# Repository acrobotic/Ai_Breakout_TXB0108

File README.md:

## Ai\_Breakout\_TXB0108

PCB design files (EAGLE) for a breakout board of the 8-channel bi-directional
Logic Level Shifter TXB0108.

## Description

For more details, check out the product page at:

   * https://acrobotic.com/brk-00014

Designed by ACROBOTIC Industries.  Please consider buying products from us to 
help fund future Open-Source projects like this! We’ll always put our best 
effort in every project, and release all our design files and code for you to 
use. 

## License

Released under the Creative Commons Attribution, Share-Alike license. Please 
check LICENSE.txt for more information. All text above must be included in any 
redistribution.

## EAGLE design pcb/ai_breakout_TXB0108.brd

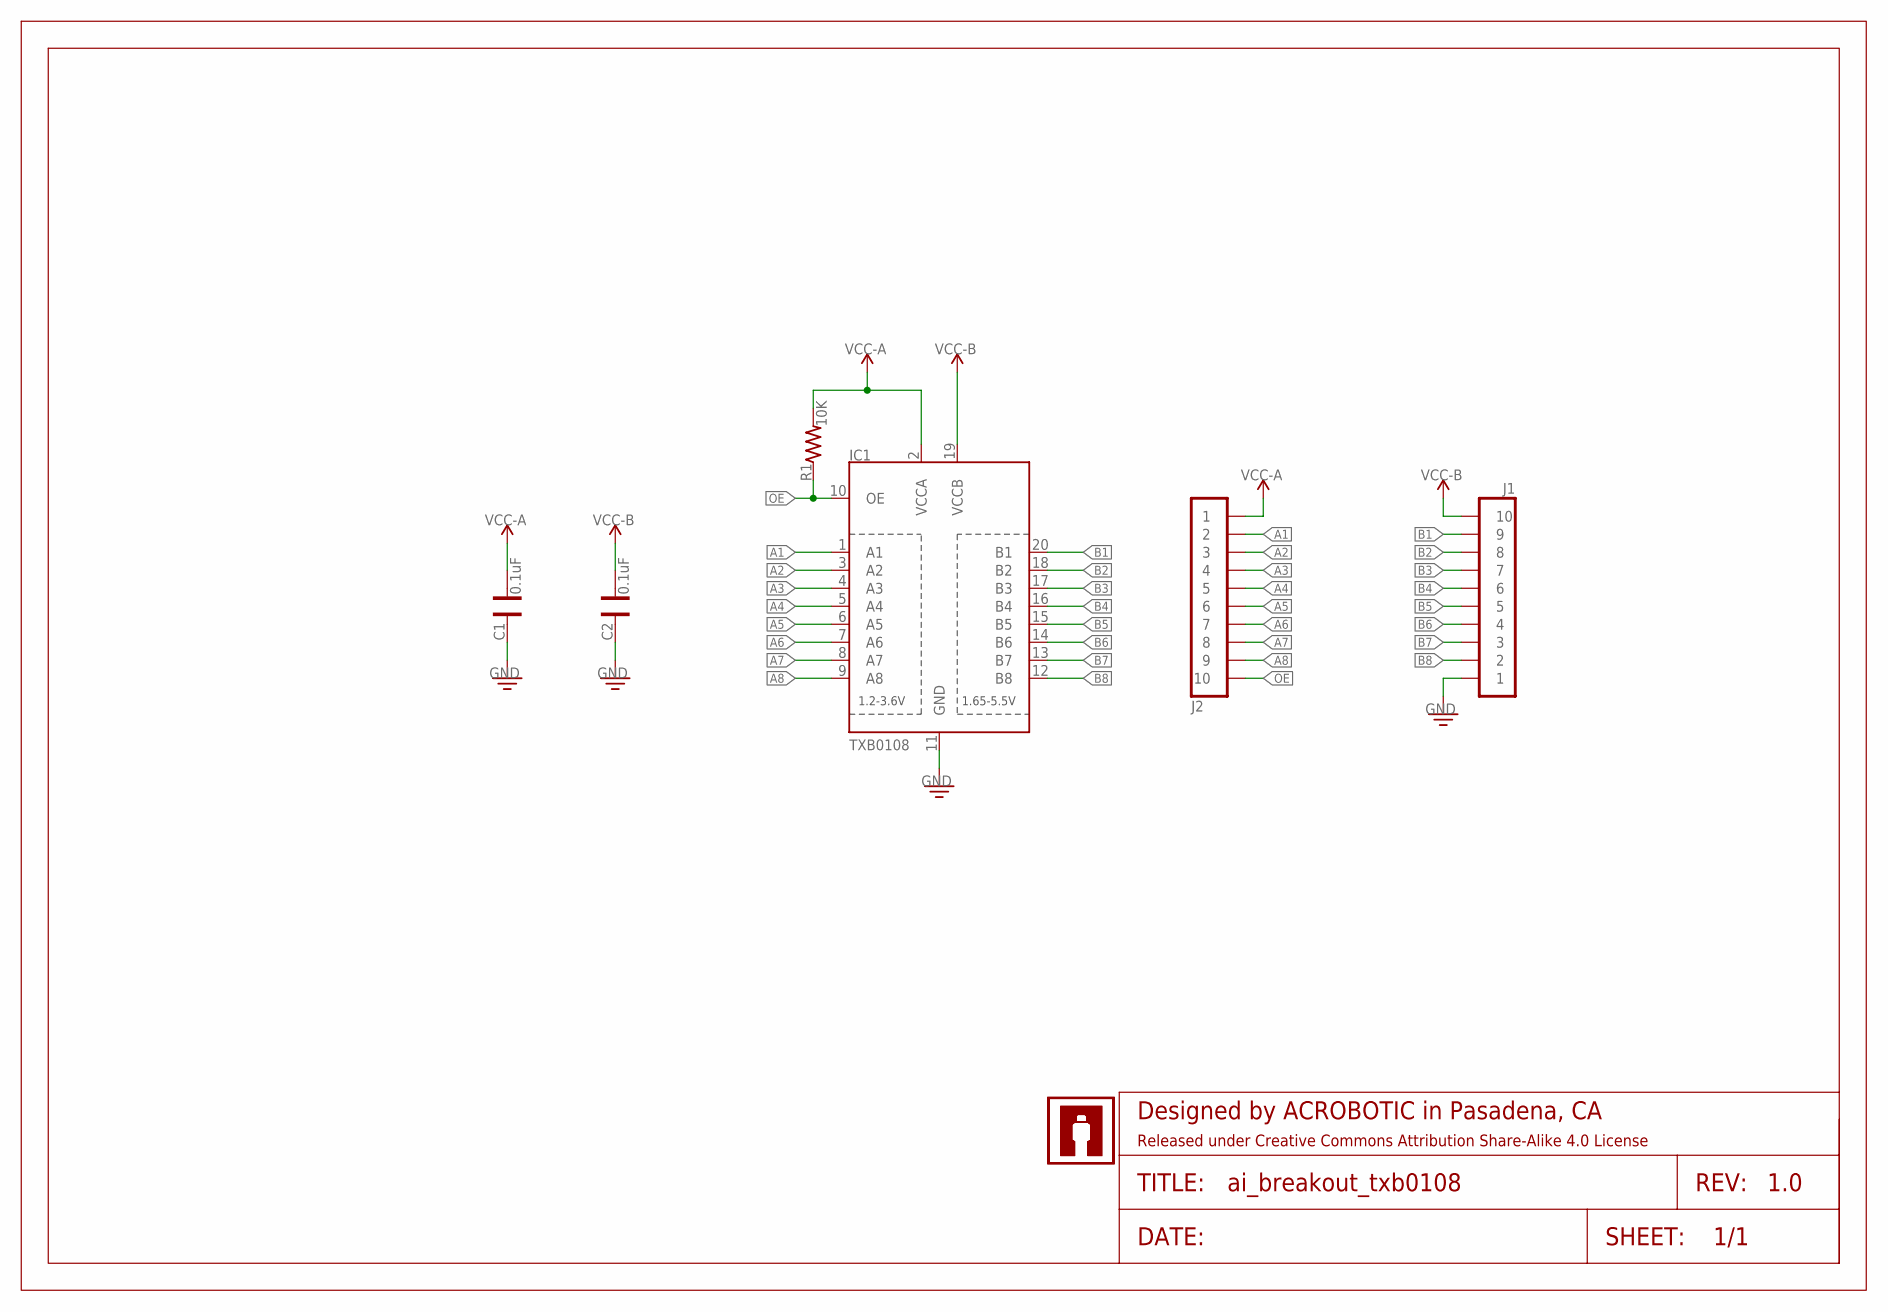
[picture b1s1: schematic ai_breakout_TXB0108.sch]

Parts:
C1, C2: 0.1uF; CAP-0603
FRAME1: FRAME-LETTER; CREATIVE-COMMONS
IC1: TXB0108; TSSOP20
J1: 1X10
J2: 1X10NOFIRST; 1X10-NOFIRST
R1: 10K; RES-0603
U$1, U$2: AI-LOGOXS; AI-LOGO-XS

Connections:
A1: IC1.1 (A1), J2.2
A2: IC1.3 (A2), J2.3
A3: IC1.4 (A3), J2.4
A4: IC1.5 (A4), J2.5
A5: IC1.6 (A5), J2.6
A6: IC1.7 (A6), J2.7
A7: IC1.8 (A7), J2.8
A8: IC1.9 (A8), J2.9
B1: IC1.20 (B1), J1.9
B2: IC1.18 (B2), J1.8
B3: IC1.17 (B3), J1.7
B4: IC1.16 (B4), J1.6
B5: IC1.15 (B5), J1.5
B6: IC1.14 (B6), J1.4
B7: IC1.13 (B7), J1.3
B8: IC1.12 (B8), J1.2
GND: C1.2, C2.2, IC1.11 (GND), J1.1
OE: IC1.10 (OE), J2.10, R1.1
VCC-A: C1.1, IC1.2 (VCCA), J2.1, R1.2
VCC-B: C2.1, IC1.19 (VCCB), J1.10

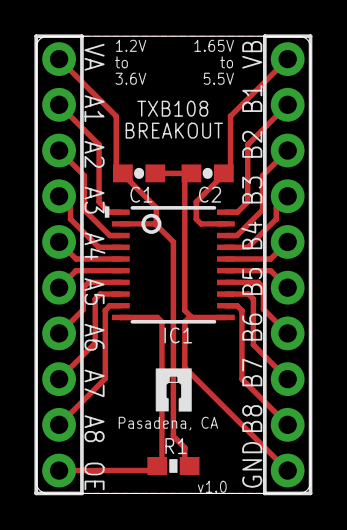
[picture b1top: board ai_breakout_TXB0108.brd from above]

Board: 2 copper layers, 15.2 x 25.4 mm, 9 parts (1 on the bottom side), 20 nets.

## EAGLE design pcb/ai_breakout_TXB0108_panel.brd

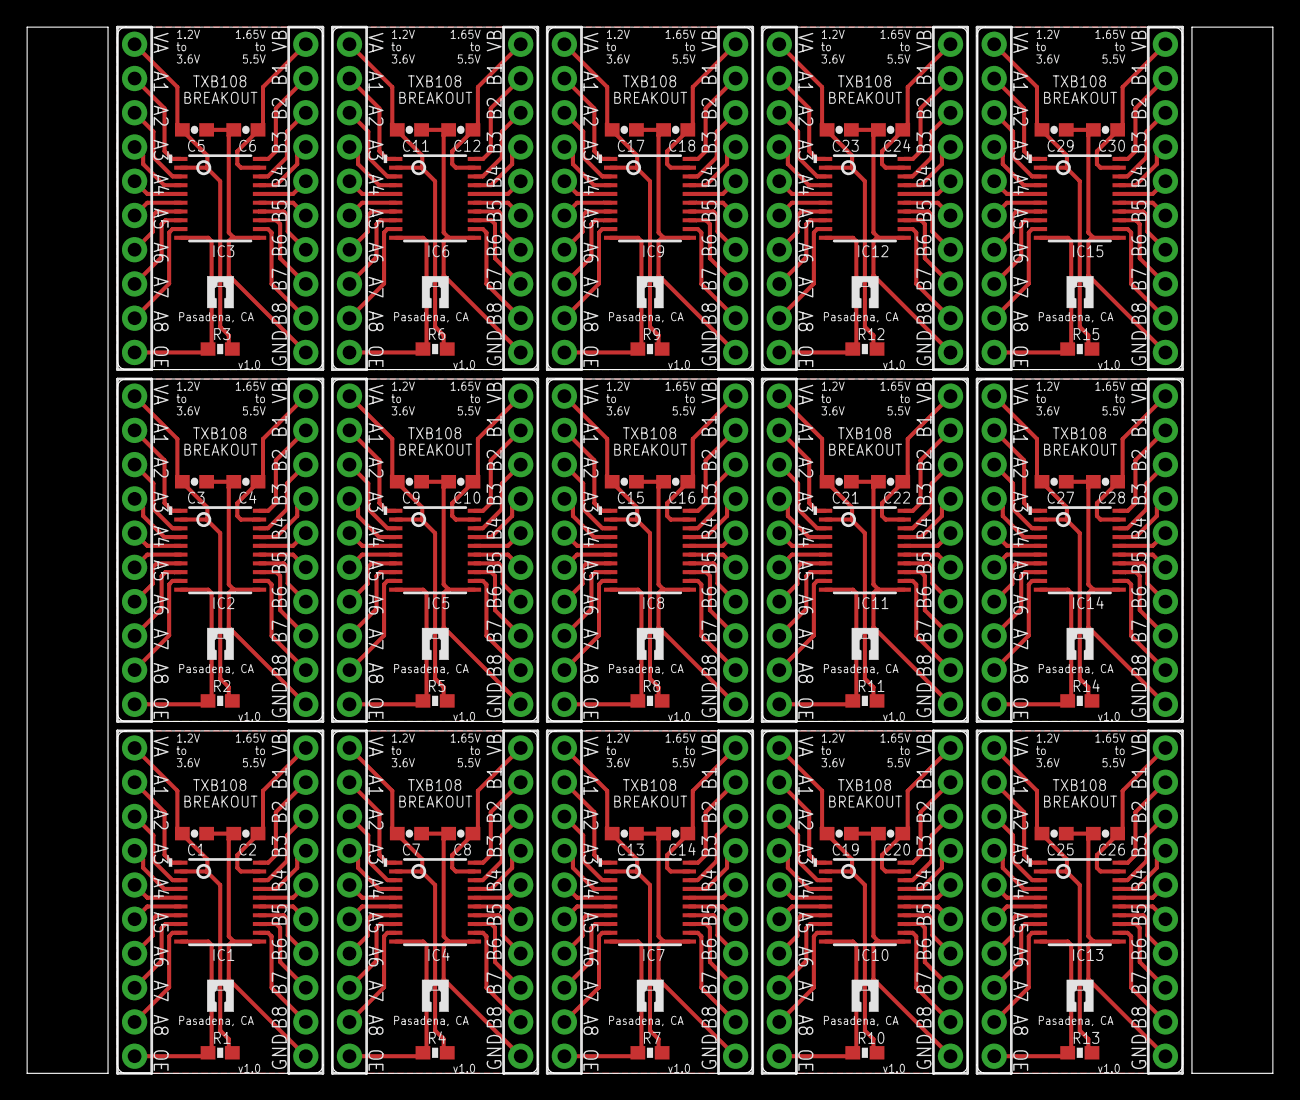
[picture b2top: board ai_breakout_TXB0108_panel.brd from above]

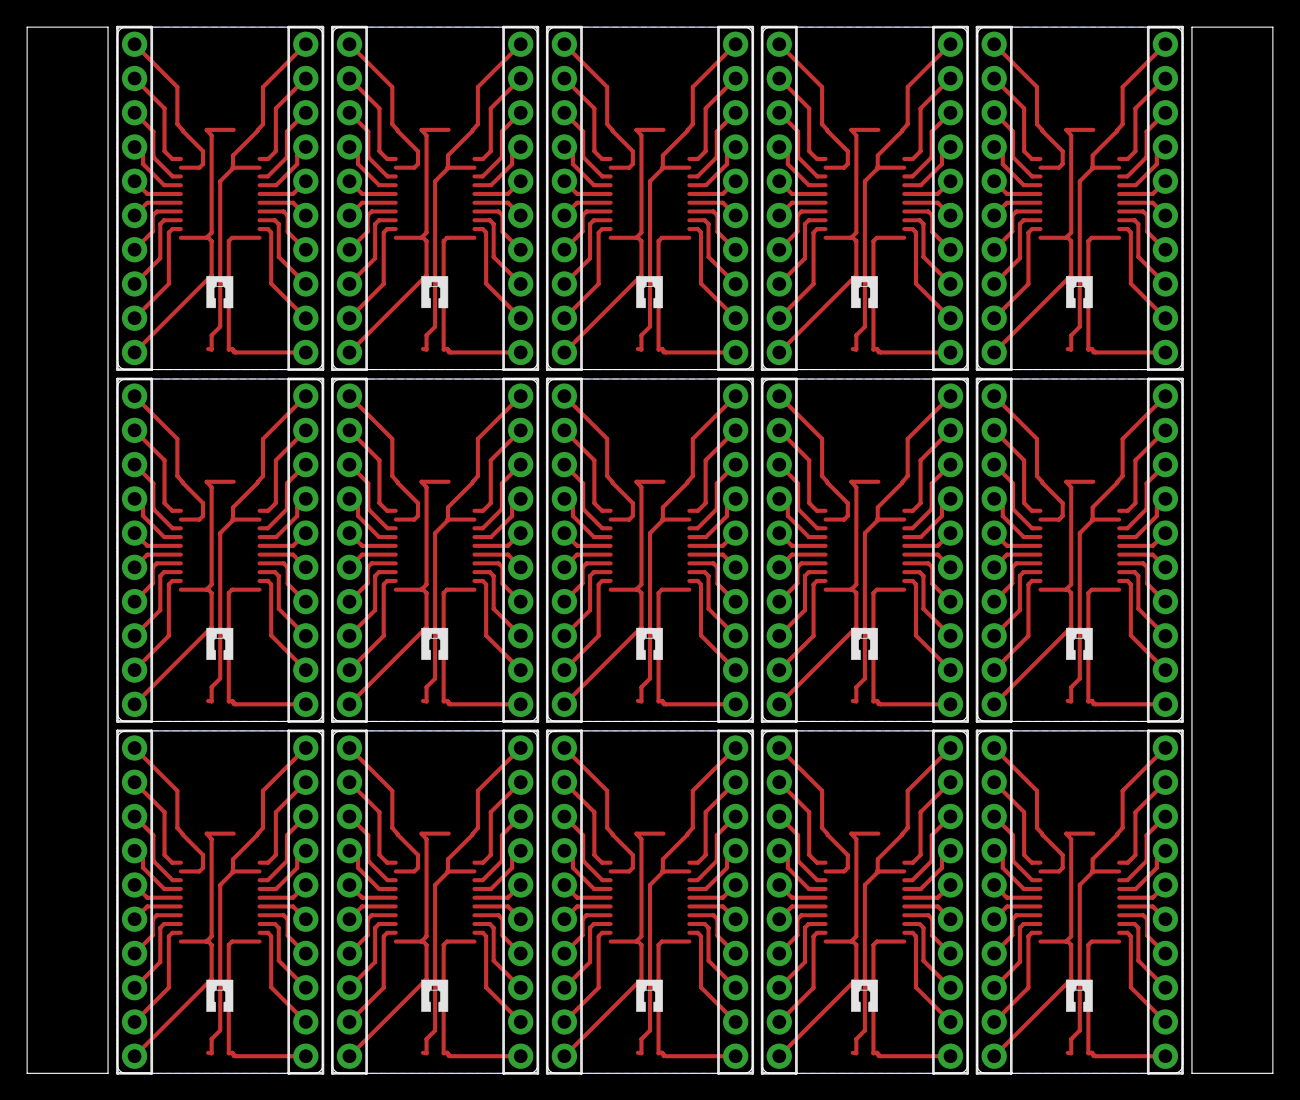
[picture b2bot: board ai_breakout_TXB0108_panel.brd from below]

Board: 2 copper layers, 92.4 x 77.6 mm, 121 parts (15 on the bottom side), 300 nets.

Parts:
C1, C2, C3, C4, C5, C6, C7, C8, C9, C10, C11, C12, C13, C14, C15, C16, C17, C18, C19, C20, C21, C22, C23, C24, C25, C26, C27, C28, C29, C30: 0.1uF; CAP-0603
FRAME1: FRAME-LETTER; CREATIVE-COMMONS
IC1, IC2, IC3, IC4, IC5, IC6, IC7, IC8, IC9, IC10, IC11, IC12, IC13, IC14, IC15: TXB0108; TSSOP20
J1, J3, J5, J7, J9, J11, J13, J15, J17, J19, J21, J23, J25, J27, J29: 1X10
J2, J4, J6, J8, J10, J12, J14, J16, J18, J20, J22, J24, J26, J28, J30: 1X10NOFIRST; 1X10-NOFIRST
R1, R2, R3, R4, R5, R6, R7, R8, R9, R10, R11, R12, R13, R14, R15: 10K; RES-0603
U$1, U$2, U$3, U$4, U$5, U$6, U$7, U$8, U$9, U$10, U$11, U$12, U$13, U$14, U$15, U$16, U$17, U$18, U$19, U$20, U$21, U$22, U$23, U$24, U$25, U$26, U$27, U$28, U$29, U$30: AI-LOGOXS; AI-LOGO-XS

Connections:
A1: IC1.1, J2.2
A2: IC1.3, J2.3
A3: IC1.4, J2.4
A4: IC1.5, J2.5
A5: IC1.6, J2.6
A6: IC1.7, J2.7
A7: IC1.8, J2.8
A8: IC1.9, J2.9
A9: IC2.1, J4.2
A10: IC2.3, J4.3
A11: IC2.4, J4.4
A12: IC2.5, J4.5
A13: IC2.6, J4.6
A14: IC2.7, J4.7
A15: IC2.8, J4.8
A16: IC2.9, J4.9
A17: IC3.1, J6.2
A18: IC3.3, J6.3
A19: IC3.4, J6.4
A20: IC3.5, J6.5
A21: IC3.6, J6.6
A22: IC3.7, J6.7
A23: IC3.8, J6.8
A24: IC3.9, J6.9
A25: IC4.1, J8.2
A26: IC4.3, J8.3
A27: IC4.4, J8.4
A28: IC4.5, J8.5
A29: IC4.6, J8.6
A30: IC4.7, J8.7
A31: IC4.8, J8.8
A32: IC4.9, J8.9
A33: IC5.1, J10.2
A34: IC5.3, J10.3
A35: IC5.4, J10.4
A36: IC5.5, J10.5
A37: IC5.6, J10.6
A38: IC5.7, J10.7
A39: IC5.8, J10.8
A40: IC5.9, J10.9
A41: IC6.1, J12.2
A42: IC6.3, J12.3
A43: IC6.4, J12.4
A44: IC6.5, J12.5
A45: IC6.6, J12.6
A46: IC6.7, J12.7
A47: IC6.8, J12.8
A48: IC6.9, J12.9
A49: IC7.1, J14.2
A50: IC7.3, J14.3
A51: IC7.4, J14.4
A52: IC7.5, J14.5
A53: IC7.6, J14.6
A54: IC7.7, J14.7
A55: IC7.8, J14.8
A56: IC7.9, J14.9
A57: IC8.1, J16.2
A58: IC8.3, J16.3
A59: IC8.4, J16.4
A60: IC8.5, J16.5
A61: IC8.6, J16.6
A62: IC8.7, J16.7
A63: IC8.8, J16.8
A64: IC8.9, J16.9
A65: IC9.1, J18.2
A66: IC9.3, J18.3
A67: IC9.4, J18.4
A68: IC9.5, J18.5
A69: IC9.6, J18.6
A70: IC9.7, J18.7
A71: IC9.8, J18.8
A72: IC9.9, J18.9
A73: IC10.1, J20.2
A74: IC10.3, J20.3
A75: IC10.4, J20.4
A76: IC10.5, J20.5
A77: IC10.6, J20.6
A78: IC10.7, J20.7
A79: IC10.8, J20.8
A80: IC10.9, J20.9
A81: IC11.1, J22.2
A82: IC11.3, J22.3
A83: IC11.4, J22.4
A84: IC11.5, J22.5
A85: IC11.6, J22.6
A86: IC11.7, J22.7
A87: IC11.8, J22.8
A88: IC11.9, J22.9
A89: IC12.1, J24.2
A90: IC12.3, J24.3
A91: IC12.4, J24.4
A92: IC12.5, J24.5
A93: IC12.6, J24.6
A94: IC12.7, J24.7
A95: IC12.8, J24.8
A96: IC12.9, J24.9
A97: IC13.1, J26.2
A98: IC13.3, J26.3
A99: IC13.4, J26.4
A100: IC13.5, J26.5
A101: IC13.6, J26.6
A102: IC13.7, J26.7
A103: IC13.8, J26.8
A104: IC13.9, J26.9
A105: IC14.1, J28.2
A106: IC14.3, J28.3
A107: IC14.4, J28.4
A108: IC14.5, J28.5
A109: IC14.6, J28.6
A110: IC14.7, J28.7
A111: IC14.8, J28.8
A112: IC14.9, J28.9
A113: IC15.1, J30.2
A114: IC15.3, J30.3
A115: IC15.4, J30.4
A116: IC15.5, J30.5
A117: IC15.6, J30.6
A118: IC15.7, J30.7
A119: IC15.8, J30.8
A120: IC15.9, J30.9
B1: IC1.20, J1.9
B2: IC1.18, J1.8
B3: IC1.17, J1.7
B4: IC1.16, J1.6
B5: IC1.15, J1.5
B6: IC1.14, J1.4
B7: IC1.13, J1.3
B8: IC1.12, J1.2
B9: IC2.12, J3.2
B10: IC2.13, J3.3
B11: IC2.14, J3.4
B12: IC2.15, J3.5
B13: IC2.16, J3.6
B14: IC2.17, J3.7
B15: IC2.18, J3.8
B16: IC2.20, J3.9
B17: IC3.12, J5.2
B18: IC3.13, J5.3
B19: IC3.14, J5.4
B20: IC3.15, J5.5
B21: IC3.16, J5.6
B22: IC3.17, J5.7
B23: IC3.18, J5.8
B24: IC3.20, J5.9
B25: IC4.12, J7.2
B26: IC4.13, J7.3
B27: IC4.14, J7.4
B28: IC4.15, J7.5
B29: IC4.16, J7.6
B30: IC4.17, J7.7
B31: IC4.18, J7.8
B32: IC4.20, J7.9
B33: IC5.12, J9.2
B34: IC5.13, J9.3
B35: IC5.14, J9.4
B36: IC5.15, J9.5
B37: IC5.16, J9.6
B38: IC5.17, J9.7
B39: IC5.18, J9.8
B40: IC5.20, J9.9
B41: IC6.12, J11.2
B42: IC6.13, J11.3
B43: IC6.14, J11.4
B44: IC6.15, J11.5
B45: IC6.16, J11.6
B46: IC6.17, J11.7
B47: IC6.18, J11.8
B48: IC6.20, J11.9
B49: IC7.12, J13.2
B50: IC7.13, J13.3
B51: IC7.14, J13.4
B52: IC7.15, J13.5
B53: IC7.16, J13.6
B54: IC7.17, J13.7
B55: IC7.18, J13.8
B56: IC7.20, J13.9
B57: IC8.12, J15.2
B58: IC8.13, J15.3
B59: IC8.14, J15.4
B60: IC8.15, J15.5
B61: IC8.16, J15.6
B62: IC8.17, J15.7
B63: IC8.18, J15.8
B64: IC8.20, J15.9
B65: IC9.12, J17.2
B66: IC9.13, J17.3
B67: IC9.14, J17.4
B68: IC9.15, J17.5
B69: IC9.16, J17.6
B70: IC9.17, J17.7
B71: IC9.18, J17.8
B72: IC9.20, J17.9
B73: IC10.12, J19.2
B74: IC10.13, J19.3
B75: IC10.14, J19.4
B76: IC10.15, J19.5
B77: IC10.16, J19.6
B78: IC10.17, J19.7
B79: IC10.18, J19.8
B80: IC10.20, J19.9
B81: IC11.12, J21.2
B82: IC11.13, J21.3
B83: IC11.14, J21.4
B84: IC11.15, J21.5
B85: IC11.16, J21.6
B86: IC11.17, J21.7
B87: IC11.18, J21.8
B88: IC11.20, J21.9
B89: IC12.12, J23.2
B90: IC12.13, J23.3
B91: IC12.14, J23.4
B92: IC12.15, J23.5
B93: IC12.16, J23.6
B94: IC12.17, J23.7
B95: IC12.18, J23.8
B96: IC12.20, J23.9
B97: IC13.12, J25.2
B98: IC13.13, J25.3
B99: IC13.14, J25.4
B100: IC13.15, J25.5
B101: IC13.16, J25.6
B102: IC13.17, J25.7
B103: IC13.18, J25.8
B104: IC13.20, J25.9
B105: IC14.12, J27.2
B106: IC14.13, J27.3
B107: IC14.14, J27.4
B108: IC14.15, J27.5
B109: IC14.16, J27.6
B110: IC14.17, J27.7
B111: IC14.18, J27.8
B112: IC14.20, J27.9
B113: IC15.12, J29.2
B114: IC15.13, J29.3
B115: IC15.14, J29.4
B116: IC15.15, J29.5
B117: IC15.16, J29.6
B118: IC15.17, J29.7
B119: IC15.18, J29.8
B120: IC15.20, J29.9
GND: C1.2, C2.2, IC1.11, J1.1
GND1: C3.2, C4.2, IC2.11, J3.1
GND2: C5.2, C6.2, IC3.11, J5.1
GND3: C7.2, C8.2, IC4.11, J7.1
GND4: C9.2, C10.2, IC5.11, J9.1
GND5: C11.2, C12.2, IC6.11, J11.1
GND6: C13.2, C14.2, IC7.11, J13.1
GND7: C15.2, C16.2, IC8.11, J15.1
GND8: C17.2, C18.2, IC9.11, J17.1
GND9: C19.2, C20.2, IC10.11, J19.1
GND10: C21.2, C22.2, IC11.11, J21.1
GND11: C23.2, C24.2, IC12.11, J23.1
GND12: C25.2, C26.2, IC13.11, J25.1
GND13: C27.2, C28.2, IC14.11, J27.1
GND14: C29.2, C30.2, IC15.11, J29.1
OE: IC1.10, J2.10, R1.1
OE1: IC2.10, J4.10, R2.1
OE2: IC3.10, J6.10, R3.1
OE3: IC4.10, J8.10, R4.1
OE4: IC5.10, J10.10, R5.1
OE5: IC6.10, J12.10, R6.1
OE6: IC7.10, J14.10, R7.1
OE7: IC8.10, J16.10, R8.1
OE8: IC9.10, J18.10, R9.1
OE9: IC10.10, J20.10, R10.1
OE10: IC11.10, J22.10, R11.1
OE11: IC12.10, J24.10, R12.1
OE12: IC13.10, J26.10, R13.1
OE13: IC14.10, J28.10, R14.1
OE14: IC15.10, J30.10, R15.1
VCC-A: C1.1, IC1.2, J2.1, R1.2
VCC-A1: C3.1, IC2.2, J4.1, R2.2
VCC-A2: C5.1, IC3.2, J6.1, R3.2
VCC-A3: C7.1, IC4.2, J8.1, R4.2
VCC-A4: C9.1, IC5.2, J10.1, R5.2
VCC-A5: C11.1, IC6.2, J12.1, R6.2
VCC-A6: C13.1, IC7.2, J14.1, R7.2
VCC-A7: C15.1, IC8.2, J16.1, R8.2
VCC-A8: C17.1, IC9.2, J18.1, R9.2
VCC-A9: C19.1, IC10.2, J20.1, R10.2
VCC-A10: C21.1, IC11.2, J22.1, R11.2
VCC-A11: C23.1, IC12.2, J24.1, R12.2
VCC-A12: C25.1, IC13.2, J26.1, R13.2
VCC-A13: C27.1, IC14.2, J28.1, R14.2
VCC-A14: C29.1, IC15.2, J30.1, R15.2
VCC-B: C2.1, IC1.19, J1.10
VCC-B1: C4.1, IC2.19, J3.10
VCC-B2: C6.1, IC3.19, J5.10
VCC-B3: C8.1, IC4.19, J7.10
VCC-B4: C10.1, IC5.19, J9.10
VCC-B5: C12.1, IC6.19, J11.10
VCC-B6: C14.1, IC7.19, J13.10
VCC-B7: C16.1, IC8.19, J15.10
VCC-B8: C18.1, IC9.19, J17.10
VCC-B9: C20.1, IC10.19, J19.10
VCC-B10: C22.1, IC11.19, J21.10
VCC-B11: C24.1, IC12.19, J23.10
VCC-B12: C26.1, IC13.19, J25.10
VCC-B13: C28.1, IC14.19, J27.10
VCC-B14: C30.1, IC15.19, J29.10

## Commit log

2014-10-19 First commit.
2014-10-19 fab version committed
2014-10-20 small update schematic
2015-03-24 Created README.md file
2015-09-29 adding additional licensing information

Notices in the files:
parts and their libraries:
Ai_Miscellany: Attribution Share-Alike 4.0 License
Ai_Miscellany: https://creativecommons.org/licenses/by-sa/4.0
Ai_Miscellany: Released under Creative Commons Attribution Share-Alike 4.0 License
